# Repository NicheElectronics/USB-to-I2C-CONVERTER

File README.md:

# USB-to-I²C Converter | FT201X

A compact USB interface for an embedded system with an I²C master. The board uses an **FTDI FT201X** to exchange data between a USB host and a microcontroller or FPGA over I²C. Its USB Type-C connector provides the USB 2.0 connection to the computer.

> **Direction matters:** The FT201X is an **I²C slave**. It cannot act as an I²C master to scan or read sensors directly. Your microcontroller or FPGA initiates every I²C transfer.

## Project status

The PCB has been assembled and tested, according to the project notes. Specific measurements, firmware, and test logs have not been included here.

## How it works

```mermaid
flowchart TD
    PC["Computer / USB host"] <-->|"USB 2.0"| FT["FT201X · I²C slave"]
    FT <-->|"SDA + SCL"| MCU["MCU or FPGA · I²C master"]
    MCU <-->|"Shared I²C bus"| SENSOR["Other I²C devices"]
```

The master can address the FT201X and other slaves on the same bus, provided each slave has a unique address and the devices share compatible I/O levels. For example, to bring sensor readings to a PC, the MCU reads the sensor and writes the result to the FT201X; the FT201X sends those bytes over USB. The PC can send commands in the other direction for the MCU to read.

This is a **USB connection for an I²C-master system**, not a PC-controlled general-purpose I²C master adapter.

## Hardware overview

| Item | Implementation / purpose |
| --- | --- |
| Bridge | FTDI FT201X, USB 2.0 full speed to I²C slave |
| USB connector | USB Type-C, wired for USB 2.0 device operation |
| USB protection | ESD protection on D+ and D−; 27 Ω series resistors in the USB data paths |
| I²C connection | SDA and SCL with pull-up resistors; MCU/FPGA provides the clock |
| I/O supply | VCCIO sets the FT201X interface voltage; match it to the I²C bus |
| Other signals | Reset and configurable CBUS signals available on the board |
| Power | USB bus power with local decoupling and bulk capacitance |

The USB Type-C connection uses both orientations of D+ and D− and separate pull-down resistors on CC1 and CC2. Check the schematic for exact values, connector pinout, headers, and power options before connecting external hardware.

## I²C address and speed

- The FT201X factory-default **7-bit address is `0x22`**. An MCU library normally expects this 7-bit value, not the shifted address bytes (`0x44` for write and `0x45` for read).
- The address is configurable in FT201X nonvolatile settings, so check the programmed configuration if a scanner does not find `0x22`.
- Start bus bring-up at **100 kHz**; try **400 kHz** after basic transfers work. The FT201X supports faster I²C modes, but the selected rate and pull-ups must also work for every other device and the bus wiring.
- The USB serial port baud setting does **not** set the I²C clock. The I²C master generates SCL.

## Bring-up

1. With power off, check for shorts between supply and ground and confirm the intended VCCIO and pull-up voltage.
2. Connect USB and confirm the FT201X enumerates on the computer. Use FTDI's **FT_PROG** if you need to inspect its programmed settings.
3. Connect a common ground, SDA, and SCL to an I²C-master MCU. Avoid connecting an incompatible-voltage bus directly.
4. Set the MCU bus to 100 kHz and scan for the configured FT201X address (`0x22` by default).
5. Test bytes in **both** directions: PC → FT201X → MCU and MCU → FT201X → PC. Use the FT201X transfer protocol in the datasheet when writing firmware.
6. Add any sensors after the bridge works; check that their addresses do not conflict.

For PC-side testing, install the applicable FTDI driver. If the device appears as a virtual COM port, a serial terminal or `pyserial` can send and receive bytes. Define framing and commands in the MCU firmware; the FT201X does not automatically turn sensor data into text lines.

## If communication fails

| Symptom | Check |
| --- | --- |
| No USB device | USB cable and connector, VBUS, supply rails, reset, D+/D− wiring and ESD parts |
| No I²C acknowledgement | Master mode, common ground, SDA/SCL wiring, pull-ups, VCCIO, configured address |
| Intermittent transfers | Pull-up strength, bus capacitance, clock rate and shared-device loading |
| USB works but no sensor data | MCU firmware, FT201X read/write sequence and sensor address |

## Reference

- [FTDI FT201X product documentation](https://ftdichip.com/products/ft201xq/)

## Author

**Nishant Patil**

No license has been specified for the project files. Add a license file when you decide how others may use the design.

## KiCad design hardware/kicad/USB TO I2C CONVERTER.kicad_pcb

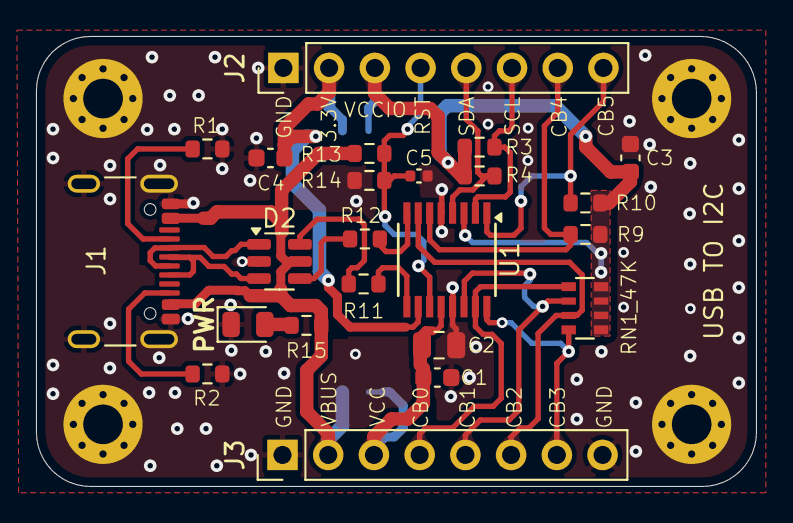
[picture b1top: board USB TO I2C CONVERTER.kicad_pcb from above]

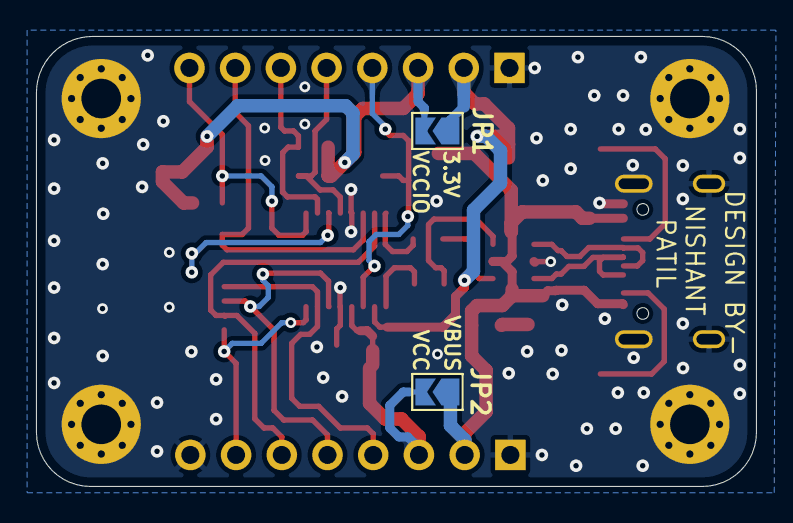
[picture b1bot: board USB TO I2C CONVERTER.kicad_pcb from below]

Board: 2 copper layers, 40.0 x 25.0 mm, 29 parts (2 on the bottom side), 23 nets.

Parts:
C1, C3, C4: 0.1u; C_0603_1608Metric
C2: 4.7u; C_0805_2012Metric
C5: 10n; C_0402_1005Metric
D2: USBLC6-2SC6; SOT-23-6
H1, H2, H3, H4: M2; MountingHole_2.2mm_M2_Pad_Via
J1: USB_C_Receptacle_USB2.0_16P; USB_C_Receptacle_GCT_USB4105-xx-A_16P_TopMnt_Horizontal
J2, J3: Conn_01x08_Pin; PinHeader_1x08_P2.54mm_Vertical
JP1, JP2: Jumper_2_Open; SolderJumper-2_P1.3mm_Open_TrianglePad1.0x1.5mm
PWR: LED; LED_0805_2012Metric
R1, R2: 5K1; R_0603_1608Metric
R3, R4: 1K; R_0603_1608Metric
R9, R10: 47K; R_0603_1608Metric
R11, R12: 27R; R_0603_1608Metric
R13: 10K; R_0603_1608Metric
R14: 15K; R_0603_1608Metric
R15: 270R; R_0603_1608Metric
RN1_47K: R_47K; R_Array_Convex_4x0603
U1: FT201XS; SSOP-16_3.9x4.9mm_P0.635mm

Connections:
3.3VOUT: C4.1, J2.2, JP1.1 (A), U1.10 (3V3OUT)
+VBUS: D2.5 (VBUS), J1.A4 (VBUS), J1.A9 (VBUS), J1.B4 (VBUS), J1.B9 (VBUS), J3.2, JP2.1 (A), R13.1, R15.1
/CBUS0: J3.4, RN1_47K.1 (R1.1), U1.15 (CBUS0)
/CBUS1: J3.5, RN1_47K.2 (R2.1), U1.14 (CBUS1)
/CBUS2: J3.6, RN1_47K.3 (R3.1), U1.7 (CBUS2)
/CBUS3: J3.7, RN1_47K.4 (R4.1), U1.16 (CBUS3)
/CBUS4: J2.7, R9.1, U1.6 (CBUS4)
/CBUS5: J2.8, R10.1, U1.1 (CBUS5)
/I2CSCL: J2.6, R3.2, U1.2 (SCL)
/I2CSDA: J2.5, R4.2, U1.4 (SDA)
/RESET: C5.1, J2.4, R13.2, R14.1, U1.11 (~RESET)
/USBCC1: J1.A5 (CC1), R1.1
/USBCC2: J1.B5 (CC2), R2.1
/USBCD+: D2.3 (I/O2), J1.A6 (D+), J1.B6 (D+)
/USBCD-: D2.1 (I/O1), J1.A7 (D-), J1.B7 (D-)
/USBD+: D2.4 (I/O2), R12.1
/USBD-: D2.6 (I/O1), R11.1
/USBDM: R11.2, U1.9 (USBDM)
/USBDP: R12.2, U1.8 (USBDP)
GND: C1.2, C2.2, C3.2, C4.2, C5.2, D2.2 (GND), H1.1, H2.1, H3.1, H4.1, J1.A1 (GND), J1.A12 (GND), J1.B1 (GND), J1.B12 (GND), J1.S1 (SHIELD), J2.1, J3.1, J3.8, PWR.1 (K), R1.2, R2.2, R14.2, U1.5 (GND), U1.13 (GND)
unnamed: PWR.2 (A), R15.2
VCC: C1.1, C2.1, J3.3, JP2.2 (B), U1.12 (VCC)
VCCIO: C3.1, J2.3, JP1.2 (B), R3.1, R4.1, R9.2, R10.2, RN1_47K.5 (R4.2), RN1_47K.6 (R3.2), RN1_47K.7 (R2.2), RN1_47K.8 (R1.2), U1.3 (VCCIO)

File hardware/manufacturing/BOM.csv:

"Reference","Qty","Value","DNP","Exclude from BOM","Exclude from Board","Footprint","Datasheet"
"C1,C3,C4","3","0.1u","","","","Capacitor_SMD:C_0603_1608Metric","~"
"C2","1","4.7u","","","","Capacitor_SMD:C_0805_2012Metric","~"
"C5","1","10n","","","","Capacitor_SMD:C_0402_1005Metric","~"
"D1","1","LED","","","","LED_SMD:LED_0805_2012Metric","~"
"D2","1","USBLC6-2SC6","","","","Package_TO_SOT_SMD:SOT-23-6","https://www.st.com/resource/en/datasheet/usblc6-2.pdf"
"H1,H2,H3,H4","4","M2","","Excluded from BOM","","MountingHole:MountingHole_2.2mm_M2_Pad_Via","~"
"J1","1","USB_C_Receptacle_USB2.0_16P","","","","Connector_USB:USB_C_Receptacle_GCT_USB4105-xx-A_16P_TopMnt_Horizontal","https://www.usb.org/sites/default/files/documents/usb_type-c.zip"
"J2,J3","2","Conn_01x08_Pin","","","","Connector_PinHeader_2.54mm:PinHeader_1x08_P2.54mm_Vertical","~"
"JP1,JP2","2","Jumper_2_Open","","","","Jumper:SolderJumper-2_P1.3mm_Open_TrianglePad1.0x1.5mm","~"
"R1,R2","2","5K1","","","","Resistor_SMD:R_0603_1608Metric","~"
"R3,R4","2","1K","","","","Resistor_SMD:R_0603_1608Metric","~"
"R9,R10","2","47K","","","","Resistor_SMD:R_0603_1608Metric","~"
"R11,R12","2","27R","","","","Resistor_SMD:R_0603_1608Metric","~"
"R13","1","10K","","","","Resistor_SMD:R_0603_1608Metric","~"
"R14","1","15K","","","","Resistor_SMD:R_0603_1608Metric","~"
"R15","1","270R","","","","Resistor_SMD:R_0603_1608Metric","~"
"RN1","1","R_47K","","","","Resistor_SMD:R_Array_Convex_4x0603","~"
"U1","1","FT201XS","","","","Package_SO:SSOP-16_3.9x4.9mm_P0.635mm","https://www.ftdichip.com/Support/Documents/DataSheets/ICs/DS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"
